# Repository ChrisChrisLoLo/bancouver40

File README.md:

# Zine Machine

> **🚧 Work in progress — not ready for fab yet.**
> Nothing here has been built or tested on real hardware. The v3 main board is routed and passes DRC, but its fab
> outputs and the "verify before ordering" checks are still open. Don't order boards from these files yet.

A pocket Linux computer built around a 40% keyboard: the [bancouver40](https://github.com/ChrisChrisLoLo/bancouver40)
4×10 Choc keyboard, a [PocketBeagle 2 Industrial](https://www.beagleboard.org/boards/pocketbeagle-2-industrial)
and a 4.58″ 320×960 bar display, battery powered, in an open 3D-printed tray.

*Blender renders of the v3 design: the routed main board from KiCad, the printed tray and display chassis, and
keycaps carrying the stock bancouver40 layers. The interactive page (<https://elevenarms.github.io/zinemachine0/>)
still shows the earlier v2 layout.*

## What it is (v3)

| | |
|---|---|
| Computer | PocketBeagle 2 Industrial (TI AM6254, 1 GB DDR4, 64 GB eMMC, −40…85 °C), face-down on its low-profile 3.55 mm sockets, USB-C out through the rear wall |
| Keyboard | 40 Kailh Choc v1 keys (4×10 ortholinear, CFX caps) plus three red/yellow/blue **mode keys**; switches soldered, no hot-swap |
| Key scanning | the PocketBeagle's own Cortex-M4F reads every key directly through six chained 74HC165s on its MCU-domain pins: no matrix, no diodes, full rollover |
| Display | 4.58″ 320×960 IPS bar panel (ST7701S), RGB565 over the AM62's VOUT0 + 3-wire SPI init, TPS61165 backlight boost |
| USB | FE1.1s hub on the PocketBeagle's USB1, two rear USB-A ports (500 mA each, TPS2051B) |
| Power | 1S LiPo (about 9 × 40 × 70 mm, ~2.5–3 Ah) under the display; IP5306 charger/5 V boost with its own rear charging USB-C; chunky slide switch; charge, power and boot LEDs |
| Audio | ES8388 codec over I2S: headset jack (headphones + mic, TRRS) and a line-out jack |
| Main board | 170 × 126 mm, 4 layers, all assembled parts on the top side; routed, DRC clean |
| Enclosure | open printed tray (175.2 × 131.2 × 12.5 mm) the whole assembly sits in; a printed display chassis holds the panel and boxes and clamps the battery; about 21 mm tall overall |

Keycap legends: base layer in the centre, Layer 1 (hold **L1**: numbers, brackets, arrows) top right in blue,
Layer 2 (hold **Space**: shifted symbols) top left in green, Layer 3 (both: F-keys, volume, Del, Boot) bottom right
in orange, hold functions bottom left.

## Repository layout

| Path | Contents |
|---|---|
| `pcb/bancouver40_pb2/` | the main board, KiCad 10 project: [v3 spec](pcb/bancouver40_pb2/DESIGN_v3.md) (positions, pin map, blocks), schematic sheets, PCB, own footprints/symbols (`zm_v3.*`), fab file |
| `tools/zm_v3/` | scripts that generate the v3 schematic and board from `design.py` and reproduce the routing (`krt_route.sh`, `finish.sh`) |
| `mech/` | FreeCAD scripts and parts: `tray`, `display_chassis` (both with fab files), `pb2_envelope` (light PocketBeagle model), `zine_concept` (whole-device layout with legends and exploded view), `fitcheck_board` (board STEP vs. mechanics) |
| `mech/render/` | Blender render script and output (`blender -b -P mech/render/zine_render.py -- 128 hero exploded`) |
| `case/pocketbeagle2/models/industrial/` | PocketBeagle 2 Industrial references: Rev A schematic, dimension drawing, [header pinout CSV](case/pocketbeagle2/models/industrial/pb2_header_pinout.csv), SysConfig |
| `case/pocketbeagle2/` | the earlier v2 case (SolidCraft), kept for reference |
| `bom/`, `site/`, `tools/pocketbeagle2/` | v2 BOM, the interactive page, and the v2 generator scripts |
| everything else | the upstream bancouver40 repository, unchanged ([original README](README-bancouver40.md)) |

Large files that are rebuilt by scripts or downloaded (the 110 MB PocketBeagle STEP conversion, assembly STEP/GLB
outputs) are git-ignored; see `.gitignore`.

## Status / open items

- Main board: silkscreen cleanup, fab outputs and README (stage 4).
- Charger choice: plain IP5306 (charge LEDs work with the device off; used now) or IP5306-I2C (Linux reads charge state).
- Check the PJ-327A headset jack's pin assignment with a plug and a meter.
- The fab stocks only 75 of the GCT USB1046 USB-A ports.
- Power budget is tight: ~2.3 A worst case against the IP5306's 2.1–2.4 A.
- Choose the battery cell and the slide switch, and decide what the three mode keys do.
- Software: M4F key-scan firmware + RPMsg-to-uinput service, device-tree overlay for the panel, codec and hub.
- From v2, still open: the display FPC pinout/contact side and fold length against a real panel.

## Credits

- **bancouver40** — keyboard design, PCB, case and firmware by **ChrisChrisLoLo (sporewoh)**:
  <https://github.com/ChrisChrisLoLo/bancouver40>, GPL-3.0. This project is a fork of it and everything in
  `pcb/bancouver40_pb2` starts from that board. The original README is kept as [README-bancouver40.md](README-bancouver40.md).
- **PocketBeagle 2 / PocketBeagle 2 Industrial** — hardware, schematic, drawings and 3D model by **BeagleBoard.org**. The STEP model
  (`case/pocketbeagle2/models/pocketbeagle2_v03_21_EVT.stp`, from <https://openbeagle.org/pocketbeagle/pocketbeagle-2>)
  is © BeagleBoard.org Foundation, [CC BY-SA 4.0](https://creativecommons.org/licenses/by-sa/4.0/); its web conversion is shared under the same licence.
  Pin functions come from the [PocketBeagle 2 documentation](https://docs.beagleboard.org/boards/pocketbeagle-2/).
- **KiCad** and the **KiCad libraries** — footprints and 3D component models (CC BY-SA 4.0 with the KiCad library exception), <https://www.kicad.org/>.
- **SolidCraft** (tangency-labs) — the case was modelled through SolidCraft's MCP server, <https://solidcraft.io/>.
- **Freerouting** — autorouting of the v2 display bus, <https://github.com/freerouting/freerouting> (not bundled).
- **KiCadRoutingTools** — routing of the v3 main board (built from source, not bundled).
- **FreeCAD** — the v3 tray, display chassis and fit checks; **Blender** — the renders.
- **three.js** (MIT) for the 3D page; **JetBrains Mono** and **Space Grotesk** (SIL OFL) via Google Fonts.
- **QMK** / **Vial** — keyboard firmware (GPL), as shipped by the upstream repo.
- Reference documents (linked, not redistributed): Maxen MX-046HS40FS-N01 / BuyDisplay ER-TFT4.58-1 panel drawing,
  Sitronix ST7701S and TI TPS61165 datasheets, Amphenol F32Q/F32R drawings.
- Design work assisted by Claude Code (Anthropic).

## License

GPL-3.0, inherited from bancouver40 (see [LICENSE](LICENSE)). The PocketBeagle 2 model and its derivatives are
CC BY-SA 4.0 (see [case/pocketbeagle2/models/README.md](case/pocketbeagle2/models/README.md)).

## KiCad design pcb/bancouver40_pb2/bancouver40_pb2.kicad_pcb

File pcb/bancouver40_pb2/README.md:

# Zine Machine v0 — PCB notes

> **Work in progress — not ready for fab.**

bancouver40 + PocketBeagle 2 + 4.58" 320x960 bar display

A variant of the bancouver40 with the board and case extended 48 mm north to carry a
[PocketBeagle 2](https://docs.beagleboard.org/boards/pocketbeagle-2/) and a 4.58" 320x960 IPS bar TFT
(ST7701S; e.g. [Maxen MX-046HS40FS-N01](https://maxen-lcddisplay.com/product/4-6-inch-bar-type-tft-display/),
BuyDisplay ER-TFT4.58-1 / Tailor Pixels TTG046XVS-01 — same 118.8 x 41.57 x 2.5 mm outline).
The keyboard matrix and ATmega32U4 are unchanged; the 32U4 is a USB keyboard wired into the
PocketBeagle's second USB port, so the stock QMK/Vial firmware works as-is.

The first version (2" Waveshare SPI LCD) is kept in `v1_2in_lcd/` and `case/pocketbeagle2/v1_2in_lcd/`.

## What changed on the PCB

| | |
|---|---|
| Outline | 170 x 116 mm (was 170 x 68), USB tab removed |
| Removed | J1 USB-C receptacle, R2/R3 (CC 5k1) |
| U2 | PocketBeagle 2 on the PocketBeagle header grid (`Module:BeagleBoard_PocketBeagle`), USB-C toward the left edge |
| J3 | 40-pin 0.5 mm FPC connector, Amphenol F32Q-1A7H1-11040 (top contact); F32R (bottom contact) has the identical land pattern |
| U3 + L1, D41, C8-C10, R7, R8 | TPS61165 white-LED boost for the backlight (2 x 4 LEDs, 11.2-13.2 V), 0.2 V / 5.1 Ω ≈ 39 mA, PWM dimming |
| H11-H13 | M2x15 standoffs that clamp the PCB to the case and hold the bezel |

Routing: the USB/VBUS links and the J1-removal repairs are hand-placed (`pcb_route.py`); the panel
bus and backlight are autorouted with Freerouting 2.5 restricted to the new nets (the keyboard's
copper is exported as fixed and never re-imported), then both layers are poured with GND and stitched.

### Display interface

The AM6254's DSS drives the panel as parallel RGB565 (DPI) on VOUT0; the ST7701S is initialised over
3-wire SPI. With the panel in 18-bit mode (MDT=1) DB17..12 = R5..R0, DB11..6 = G5..G0, DB5..0 = B5..B0:

| Panel (J3 pin) | PocketBeagle 2 | | Panel (J3 pin) | PocketBeagle 2 |
|---|---|---|---|---|
| DB17-DB13 (33-29) | VOUT0_D15..D11 = P2.34, P1.31, P2.30, P2.32, P1.33 | | PCLK (12) | P2.17 |
| DB12, DB0 (28, 16) | GND (R/B LSBs) | | DE (13) | P1.29 |
| DB11-DB6 (27-22) | VOUT0_D10..D5 = P1.36, P2.35, P2.18, P2.33, P2.24, P1.20 | | VSYNC / HSYNC (14 / 15) | P2.22 / P2.28 |
| DB5-DB1 (21-17) | VOUT0_D4..D0 = P2.20, P2.08, P2.06, P2.04, P2.02 | | SDA / SCK / CS (9 / 10 / 11) | P2.25 / P2.29 / P2.31 (SPI0) |
| VCI (5) | +3V3 (P2.23) | | RESET (6) | P2.10 (GPIO0_91) |
| LEDA / LEDK (1 / 2-3) | boost output / current sense | | Backlight PWM | P2.01 (ECAP2 APWM, mode 2) |

Pin functions verified against the PocketBeagle 2 pinmux tables
(docs.beagleboard.org/boards/pocketbeagle-2/04-expansion.html). **VOUT0_D10 and D11 share their header
pins with I2C1 (P1.36/P1.33 have a second ball each): leave the I2C1 balls unmuxed.** The panel's touch
pins (35-39) are left unconnected.

USB and power are as before: D-/D+ to P1.09/P1.11 (USB1 host), P1.24 VOUT -> F1 -> the keyboard's +5V
(also feeds the backlight boost), P1.05 USB1_VBUS left open.

Checks (KiCad 10.0.7 `kicad-cli`): 0 unconnected items; ERC and schematic parity show only what the
original project already has (KiCad 6 -> 10 auto-net naming, R4/R5 value fields, C3 thermal, U1 PC6).
Minimum track width is 0.12 mm (Freerouting necks to 0.187 mm, once 0.125 mm, at the 0.5 mm-pitch pads).

## Stack-up (case coordinates, z from the case bottom)

| z (mm) | |
|---|---|
| 0-1 | case floor |
| 4.5-6.1 | keyboard PCB on the original bosses + 3 through-bosses |
| 6.1-~8 | J3 connector; the panel FPC returns under the panel at ~7.4 |
| 6.1-12 | Choc v1 switches; CFX keycaps 12-15.6 |
| 6.1-14.6 | PocketBeagle 2's own 2x18 female sockets (8.5 mm) on a 2x18 male header inserted from under the PCB |
| 14.6-16.1 | PocketBeagle 2 board; tallest part under the panel 17.2, USB-C 15.1-19.3 (official BeagleBoard STEP) |
| 18.6-21.1 | bar panel, glued to the bezel's underside inside a locating frame |
| 21.1-22.6 | bezel, sitting on 3 x M2x15 standoffs (keyboard walls stay at 12.5) |

## Before ordering — verify these

1. **FPC contact side.** The panel drawing shows the stiffener on the front of the unfolded tail, so after
   the 180° fold under the panel the contacts face up -> top-contact F32Q. If your panel's contacts are on
   the other side, fit the F32R (same footprint).
2. **FPC fold length.** The 30 mm tail is budgeted as 1 mm straight + ~19 mm fold (r ≈ 6.1) + ~10 mm
   return into J3 (cable end at x ≈ 209.8 KiCad). Lay a real panel on a printout before committing.
3. **PocketBeagle mounting.** It plugs in on its factory sockets: fit a 2x18 male header from *under* the
   keyboard PCB (plastic below, pins up), trimmed to < 3 mm below the PCB (floor clearance). The design
   was checked against BeagleBoard's `pocketbeagle2_v03_21_EVT.stp` (an EVT revision).
4. **P1.24 VOUT is 5 V on PocketBeagle 2** (classic: `VOUT-5V`; PB2 docs just say `VOUT`). Measure it.
5. **PocketBeagle 2 USB-C position** (case opening 14 mm wide, centred on the short edge) and the
   microSD — it is under the panel now, so flash the card before assembly.
6. **Software:** a device-tree overlay for the DSS (RGB565, PCLK on P2.17, panel timings) plus the
   ST7701S init sequence (the vendor sends one; Linux has `panel-sitronix-st7701`).

## Regenerate

```sh
tools/pocketbeagle2/build_pcb.sh pcb/bancouver40_cfx/bancouver40_cfx.kicad_pcb pcb/bancouver40_pb2/bancouver40_pb2.kicad_pcb
python3 tools/pocketbeagle2/sch_update.py pcb/bancouver40_cfx/bancouver40_cfx.kicad_sch pcb/bancouver40_pb2/bancouver40_pb2.kicad_sch
python3 tools/pocketbeagle2/case_v2.py case/pocketbeagle2      # SolidCraft command scripts
```

Needs KiCad 10 (`~/Applications/KiCad`), Java >= 25 (`brew install openjdk`) and
`~/.local/share/freerouting/freerouting-2.5.0.jar`. Freerouting is not deterministic: the script retries
until a run finishes fully routed, so each rebuild gives slightly different (equally valid) copper.

The interactive site is `site/` (serve the repo root, open `/site/`). The case is `case/pocketbeagle2/bancouver40_pb2.solidcraft`; `stage1..5*.json` built it through the
SolidCraft MCP server (`tools/pocketbeagle2/sc.py`). `REF_*` bodies (PCB, PocketBeagle, panel, FPC,
connector, standoffs, 40 Choc switches and CFX keycaps) are fit-check placeholders, left out of the
STL/STEP print files.

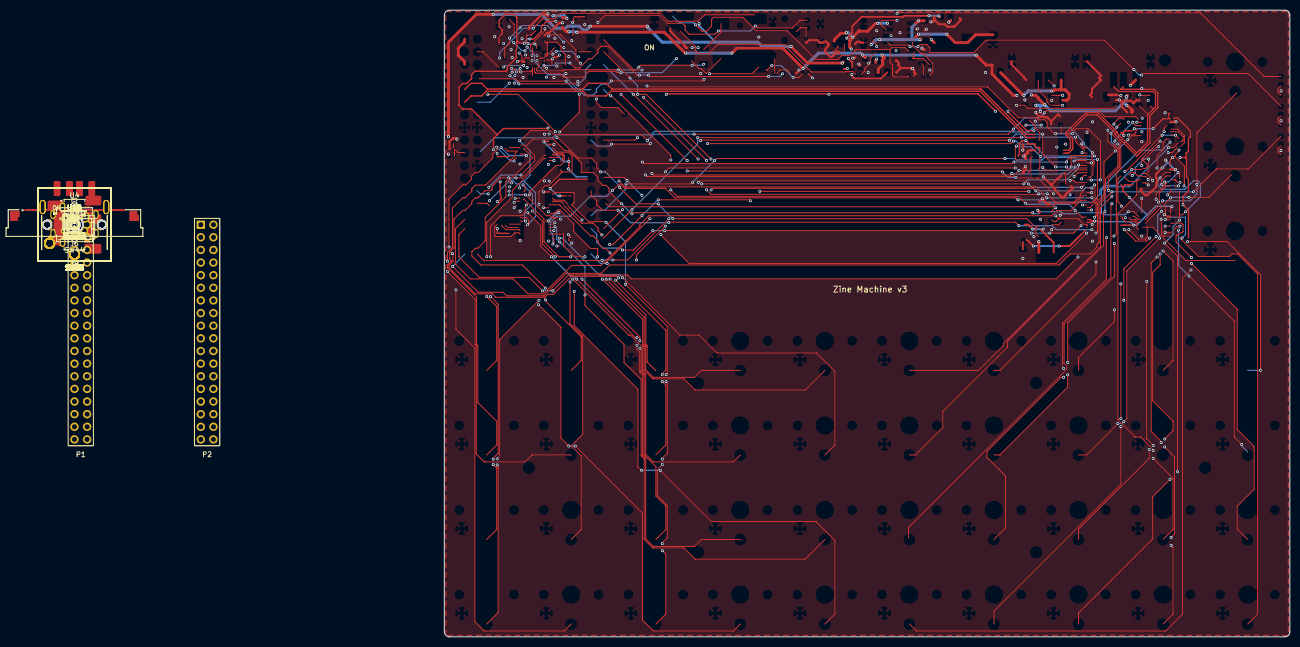
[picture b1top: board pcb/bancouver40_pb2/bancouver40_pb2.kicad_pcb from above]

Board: 4 copper layers, 170.0 x 126.0 mm, 188 parts (0 on the bottom side), 156 nets.

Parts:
C1: 4.7uF 25V; C_0805_2012Metric
C2: 1uF 50V; C_0805_2012Metric
C3: 220nF; C_0603_1608Metric
C10, C12, C14, C16, C18, C27, C31, C40, C41, C42, C44, C46, C49, C52, C60, C61, C62, C63, C64, C65: 100nF; C_0402_1005Metric
C11, C13, C20, C21, C43, C45, C47, C48, C50, C51, C55, C58, C59, C66: 10uF; C_0603_1608Metric
C15, C17, C56, C57: 100uF; C_1206_3216Metric
C22, C23, C24, C25, C26, C28, C29: 22uF; C_0805_2012Metric
C30, C53, C67: 1uF; C_0402_1005Metric
C54: 10nF; C_0402_1005Metric
D1: B5819W; D_SOD-123
D2: red CHG; LED_0603_1608Metric
D3: green PWR; LED_0603_1608Metric
D4: yellow BOOT; LED_0603_1608Metric
H1, H2, H3, H4, H5, H6: M2; MountingHole_2.2mm_M2_ISO7380
H7, H8, H9, H10: M2; MountingHole_2.2mm_M2
J3: F32Q-1A7H1-11040; Amphenol_F32Q-1A7x1-11040_1x40-1MP_P0.5mm_Horizontal
J5: LiPo 1S; JST_PH_B2B-PH-K_1x02_P2.00mm_Vertical
J6: USB-C 6P; USB_C_Receptacle_6P_ShouHan
J7, J8: USB-A; USB_A_GCT_USB1046
J9: Headset (CTIA); Jack_3.5mm_PJ-327A_5JJ
J10: Line out; Jack_3.5mm_PJ-320A-3P_DIP
L1: 22uH; L_Changjiang_FNR4030S
L2: 1uH; L_Sunlord_MWSA0603S
Q1: AO3401A; SOT-23
Q2: AO3400A; SOT-23
R1: 5.1R 1%; R_0603_1608Metric
R2, R26, R53: 100k; R_0402_1005Metric
R10: 2.7k 1%; R_0603_1608Metric
R11, R12, R13, R27, R47, R48: 10k; R_0402_1005Metric
R20, R21: 5.1k; R_0402_1005Metric
R22: 2R; R_0603_1608Metric
R23: 0.5R; R_0603_1608Metric
R24, R25, R30, R33, R51: 1k; R_0402_1005Metric
R28, R31, R32: 1M; R_0402_1005Metric
R29: 470k; R_0402_1005Metric
R40, R41, R42, R43, R44, R60, R61: 33R; R_0402_1005Metric
R45, R46, R52: 2.2k; R_0402_1005Metric
R49, R50: 47k; R_0402_1005Metric
RN1, RN2, RN3, RN4, RN5, RN6, RN7, RN8, RN9, RN10, RN11, RN12: 4x10k; R_Array_Convex_4x0603
SW1, SW2, SW3, SW4, SW5, SW6, SW7, SW8, SW9, SW10, SW11, SW12, SW13, SW14, SW15, SW16, SW17, SW18, SW19, SW20, SW21, SW22, SW23, SW24, SW25, SW26, SW27, SW28, SW29, SW30, SW31, SW32, SW33, SW34, SW35, SW36, SW37, SW38, SW39, SW40, SW41, SW42, SW43: Choc_v1; SW_Kailh_Choc_V1_Plain
SW44: SK22D02G4; SW_Slide_DPDT_SK22D02G4_Angled
TP1: M4F_SPARE; TestPoint_Pad_D1.0mm
U2: PocketBeagle 2 Industrial; PocketBeagle2_FaceDown
U3: TPS61165DBVR; SOT-23-6
U4: FE1.1s; SSOP-28_3.9x9.9mm_P0.635mm
U5, U6: TPS2051BDBVR; SOT-23-5
U7, U8: USBLC6-2SC6; SOT-23-6
U9: IP5306; SOIC-8-1EP_3.9x4.9mm_P1.27mm_EP2.29x3mm
U10, U11, U12, U13, U14, U15: 74HC165; TSSOP-16_4.4x5mm_P0.65mm
U16: TPS73633DBVR; SOT-23-5
U17: ES8388; QFN-28-1EP_4x4mm_P0.4mm_EP2.4x2.4mm
X1: 12.288MHz; Oscillator_SMD_Abracon_ASE-4Pin_3.2x2.5mm
Y1: 12MHz; Crystal_SMD_3225-4Pin_3.2x2.5mm

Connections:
+3V3: C40.1, C41.1, C42.1, C43.1, C60.1, C61.1, C62.1, C63.1, C64.1, C65.1, J3.5, R45.1, R46.1, R53.1, RN1.5, RN1.6, RN1.7, RN1.8, RN2.5, RN2.6, RN2.7, RN2.8, RN3.5, RN3.6, RN3.7, RN3.8, RN4.5, RN4.6, RN4.7, RN4.8, RN5.5, RN5.6, RN5.7, RN5.8, RN6.5, RN6.6, RN6.7, RN6.8, RN7.5, RN7.6, RN7.7, RN7.8, RN8.5, RN8.6, RN8.7, RN8.8, RN9.5, RN9.6, RN9.7, RN9.8, RN10.5, RN10.6, RN10.7, RN10.8, RN11.5, RN11.6, RN11.7, RN11.8, RN12.5, RN12.6, RN12.7, RN12.8, U2.14, U2.59, U10.16, U11.16, U12.16, U13.16, U14.16, U15.16, U17.2, U17.3, X1.1, X1.4
+5V_BOOST: C24.1, C25.1, C26.1, C27.2, Q1.2, R26.2, U9.8
+5V_SYS: C1.1, C11.1, C12.1, C16.1, C18.1, C28.1, C29.1, C53.1, L1.1, Q1.3, U2.1, U2.5, U3.1, U4.20, U5.4, U5.5, U6.4, U6.5, U16.1, U16.3
/Audio/CODEC_ADCVREF: C50.1, U17.19
/Audio/CODEC_VMID: C51.1, C52.1, U17.20
/Audio/CODEC_VREF: C48.1, C49.1, U17.10
/Audio/HP_L: C56.2, J9.2, R47.1
/Audio/HP_L_C: C56.1, U17.12
/Audio/HP_R: C57.2, J9.4, R48.1
/Audio/HP_R_C: C57.1, U17.11
/Audio/I2S_ADC_C: R43.1, U17.8
/Audio/I2S_BCLK_C: R41.1, U17.5
/Audio/I2S_DAC_C: R44.2, U17.6
/Audio/I2S_LRCK_C: R42.1, U17.7
/Audio/LDO_NR: C54.1, U16.4
/Audio/LO_L: C58.2, J10.4, R49.1
/Audio/LO_L_C: C58.1, U17.15
/Audio/LO_R: C59.2, J10.2, R50.1
/Audio/LO_R_C: C59.1, U17.14
/Audio/MCLK: R40.2, U17.1
/Audio/MCLK_OSC: R40.1, X1.3
/Audio/MIC: C67.1, J9.1, R52.2
/Audio/MIC_BIAS_F: C66.1, R51.2, R52.1
/Audio/MIC_IN: C67.2, U17.24
/Keys and scan chain/K00: RN1.1, SW1.1, U10.11
/Keys and scan chain/K01: RN2.1, SW2.1, U10.3
/Keys and scan chain/K02: RN3.1, SW3.1, U11.11
/Keys and scan chain/K03: RN4.1, SW4.1, U11.3
/Keys and scan chain/K04: RN5.1, SW5.1, U12.11
/Keys and scan chain/K05: RN7.1, SW6.1, U13.11
/Keys and scan chain/K06: RN8.1, SW7.1, U13.3
/Keys and scan chain/K07: RN9.1, SW8.1, U14.11
/Keys and scan chain/K08: RN10.1, SW9.1, U14.3
/Keys and scan chain/K09: RN11.1, SW10.1, U15.11
/Keys and scan chain/K10: RN1.2, SW11.1, U10.12
/Keys and scan chain/K11: RN2.2, SW12.1, U10.4
/Keys and scan chain/K12: RN3.2, SW13.1, U11.12
/Keys and scan chain/K13: RN4.2, SW14.1, U11.4
/Keys and scan chain/K14: RN5.2, SW15.1, U12.12
/Keys and scan chain/K15: RN7.2, SW16.1, U13.12
/Keys and scan chain/K16: RN8.2, SW17.1, U13.4
/Keys and scan chain/K17: RN9.2, SW18.1, U14.12
/Keys and scan chain/K18: RN10.2, SW19.1, U14.4
/Keys and scan chain/K19: RN11.2, SW20.1, U15.12
/Keys and scan chain/K20: RN1.3, SW21.1, U10.13
/Keys and scan chain/K21: RN2.3, SW22.1, U10.5
/Keys and scan chain/K22: RN3.3, SW23.1, U11.13
/Keys and scan chain/K23: RN4.3, SW24.1, U11.5
/Keys and scan chain/K24: RN5.3, SW25.1, U12.13
/Keys and scan chain/K25: RN7.3, SW26.1, U13.13
/Keys and scan chain/K26: RN8.3, SW27.1, U13.5
/Keys and scan chain/K27: RN9.3, SW28.1, U14.13
/Keys and scan chain/K28: RN10.3, SW29.1, U14.5
/Keys and scan chain/K29: RN11.3, SW30.1, U15.13
/Keys and scan chain/K30: RN1.4, SW31.1, U10.14
/Keys and scan chain/K31: RN2.4, SW32.1, U10.6
/Keys and scan chain/K32: RN3.4, SW33.1, U11.14
/Keys and scan chain/K33: RN4.4, SW34.1, U11.6
/Keys and scan chain/K34: RN5.4, SW35.1, U12.14
/Keys and scan chain/K35: RN7.4, SW36.1, U13.14
/Keys and scan chain/K36: RN8.4, SW37.1, U13.6
/Keys and scan chain/K37: RN9.4, SW38.1, U14.14
/Keys and scan chain/K38: RN10.4, SW39.1, U14.6
/Keys and scan chain/K39: RN11.4, SW40.1, U15.14
/Keys and scan chain/KEY_CLK: R60.2, U10.2, U11.2, U12.2, U13.2, U14.2, U15.2
/Keys and scan chain/KEY_S1: U10.10, U11.9
/Keys and scan chain/KEY_S2: U11.10, U12.9
/Keys and scan chain/KEY_S3: U12.10, U13.9
/Keys and scan chain/KEY_S4: U13.10, U14.9
/Keys and scan chain/KEY_S5: U14.10, U15.9
/Keys and scan chain/KEY_SHLD: R61.2, U10.1, U11.1, U12.1, U13.1, U14.1, U15.1
/Keys and scan chain/K_BLU: RN12.3, SW43.1, U15.5
/Keys and scan chain/K_RED: RN12.1, SW41.1, U15.3
/Keys and scan chain/K_YEL: RN12.2, SW42.1, U15.4
/Keys and scan chain/U12_SPE: RN6.1, U12.3
/Keys and scan chain/U12_SPF: RN6.2, U12.4
/Keys and scan chain/U12_SPG: RN6.3, U12.5
/Keys and scan chain/U12_SPH: RN6.4, U12.6
/Keys and scan chain/U15_SPH: RN12.4, U15.6
/PocketBeagle 2 + display/BL_COMP: C3.1, U3.5
/PocketBeagle 2 + display/BL_LEDA: C2.1, D1.1, J3.1
/PocketBeagle 2 + display/BL_LEDK: J3.2, J3.3, R1.1, U3.6
/PocketBeagle 2 + display/BL_PWM: R2.1, U2.6, U3.2
/PocketBeagle 2 + display/BL_SW: D1.2, L1.2, U3.3
/PocketBeagle 2 + display/BOOT_LED_K: D4.1, R33.1
/PocketBeagle 2 + display/LCD_CS: J3.11, U2.67
/PocketBeagle 2 + display/LCD_DE: J3.13, U2.29
/PocketBeagle 2 + display/LCD_HSYNC: J3.15, U2.64
/PocketBeagle 2 + display/LCD_PCLK: J3.12, U2.53
/PocketBeagle 2 + display/LCD_RESET: J3.6, U2.46
/PocketBeagle 2 + display/LCD_SCK: J3.10, U2.65
/PocketBeagle 2 + display/LCD_SDA: J3.9, U2.61
/PocketBeagle 2 + display/LCD_VSYNC: J3.14, U2.58
/PocketBeagle 2 + display/LED_BOOT: D4.2, U2.35
/PocketBeagle 2 + display/M4F_SPARE: TP1.1, U2.43
/PocketBeagle 2 + display/VOUT_D0: J3.17, U2.38
/PocketBeagle 2 + display/VOUT_D1: J3.18, U2.40
/PocketBeagle 2 + display/VOUT_D2: J3.19, U2.42
/PocketBeagle 2 + display/VOUT_D3: J3.20, U2.44
/PocketBeagle 2 + display/VOUT_D4: J3.21, U2.56
/PocketBeagle 2 + display/VOUT_D5: J3.22, U2.20
/PocketBeagle 2 + display/VOUT_D6: J3.23, U2.60
/PocketBeagle 2 + display/VOUT_D7: J3.24, U2.69
/PocketBeagle 2 + display/VOUT_D8: J3.25, U2.54
/PocketBeagle 2 + display/VOUT_D9: J3.26, U2.71
/PocketBeagle 2 + display/VOUT_D10: J3.27, U2.36
/PocketBeagle 2 + display/VOUT_D11: J3.29, U2.33
/PocketBeagle 2 + display/VOUT_D12: J3.30, U2.68
/PocketBeagle 2 + display/VOUT_D13: J3.31, U2.66
/PocketBeagle 2 + display/VOUT_D14: J3.32, U2.31
/PocketBeagle 2 + display/VOUT_D15: J3.33, U2.70
/USB hub and power/BAT_SNUB: C23.1, R23.2
/USB hub and power/CHG_CC1: J6.A5, R20.1
/USB hub and power/CHG_CC2: J6.B5, R21.1
/USB hub and power/CHG_LED_K: D2.1, R24.1
/USB hub and power/CHG_SNUB: C21.1, R22.2
/USB hub and power/CHG_SW: L2.1, U9.7
/USB hub and power/HUB_DRV: R13.1, U4.22
/USB hub and power/HUB_REXT: R10.1, U4.14
/USB hub and power/HUB_RST: C10.1, R11.2, U4.17
/USB hub and power/HUB_XI: U4.3, Y1.1
/USB hub and power/HUB_XO: U4.2, Y1.3
/USB hub and power/LED_CHG: D2.2, U9.2
/USB hub and power/LED_PWR: D3.2, U9.4
/USB hub and power/PWR_GATE: C27.1, Q1.1, R26.1, R27.2
/USB hub and power/PWR_KEY: R30.2, U9.5
/USB hub and power/PWR_KEY_C: C30.1, R28.1, SW44.6
/USB hub and power/PWR_KEY_D: Q2.3, R30.1
/USB hub and power/PWR_KEY_G: C30.2, Q2.1, R29.1
/USB hub and power/PWR_LED_K: D3.1, R25.1
/USB hub and power/PWR_SW: R27.1, SW44.2
/USB hub and power/USB1_N: J7.2, U4.10, U7.1, U7.6
/USB hub and power/USB1_P: J7.3, U4.11, U7.3, U7.4
/USB hub and power/USB1_VBUS: C15.1, J7.1, U5.1, U7.5
/USB hub and power/USB2_N: J8.2, U4.8, U8.1, U8.6
/USB hub and power/USB2_P: J8.3, U4.9, U8.3, U8.4
/USB hub and power/USB2_VBUS: C17.1, J8.1, U6.1, U8.5
/USB hub and power/USB_OC_N: R12.2, U4.26, U5.3, U6.3
AVDD_3V3: C44.1, C45.1, C46.1, C47.1, C55.1, R51.1, U16.5, U17.16, U17.17
GND: C1.2, C2.2, C3.2, C10.2, C11.2, C12.2, C13.2, C14.2, C15.2, C16.2, C17.2, C18.2, C20.2, C21.2, C22.2, C23.2, C24.2, C25.2, C26.2, C28.2, C29.2, C31.2, C40.2, C41.2, C42.2, C43.2, C44.2, C45.2, C46.2, C47.2, C48.2, C49.2, C50.2, C51.2, C52.2, C53.2, C54.2, C55.2, C60.2, C61.2, C62.2, C63.2, C64.2, C65.2, C66.2, J3.4, J3.16, J3.28, J3.34, J3.40, J3.MP, J5.2, J6.7, J6.A12, J6.B12, J7.4, J7.SH, J8.4, J8.SH, J9.3, J10.3, Q2.2, R1.2, R2.2, R10.2, R13.2, R20.2, R21.2, R24.2, R25.2, R28.2, R29.2, R32.2, R33.2, R47.2, R48.2, R49.2, R50.2, SW1.2, SW2.2, SW3.2, SW4.2, SW5.2, SW6.2, SW7.2, SW8.2, SW9.2, SW10.2, SW11.2, SW12.2, SW13.2, SW14.2, SW15.2, SW16.2, SW17.2, SW18.2, SW19.2, SW20.2, SW21.2, SW22.2, SW23.2, SW24.2, SW25.2, SW26.2, SW27.2, SW28.2, SW29.2, SW30.2, SW31.2, SW32.2, SW33.2, SW34.2, SW35.2, SW36.2, SW37.2, SW38.2, SW39.2, SW40.2, SW41.2, SW42.2, SW43.2, SW44.1, SW44.7, SW44.8, U2.15, U2.16, U2.22, U2.51, U2.57, U3.4, U4.1, U5.2, U6.2, U7.2, U8.2, U9.9, U10.8, U10.15, U11.8, U11.15, U12.8, U12.15, U13.8, U13.15, U14.8, U14.15, U15.8, U15.10, U15.15, U16.2, U17.4, U17.13, U17.18, U17.26, U17.29, X1.2, Y1.2, Y1.4
HP_DET: J9.5, R53.2, U2.8
HUB_3V3: C13.1, C14.1, R11.1, R12.1, U4.18, U4.19, U4.21
I2C_SCL: R45.2, U2.45, U17.28
I2C_SDA: R46.2, U2.47, U17.27
I2S_ADC: R43.2, U2.12
I2S_BCLK: R41.2, U2.37
I2S_DAC: R44.1, U2.39
I2S_LRCK: R42.2, U2.4
KEY_CLK_PB: R60.1, U2.26
KEY_QH: U2.41, U10.9
KEY_SHLD_PB: R61.1, U2.28
USB_UP_N: U2.9, U4.15
USB_UP_P: U2.11, U4.16
VBAT: C22.1, J5.1, L2.2, R23.1, R31.1, SW44.5, U9.3, U9.6
VBAT_SENSE: C31.1, R31.2, R32.1, U2.19
VIN_CHG: C20.1, J6.A9, J6.B9, R22.1, U9.1

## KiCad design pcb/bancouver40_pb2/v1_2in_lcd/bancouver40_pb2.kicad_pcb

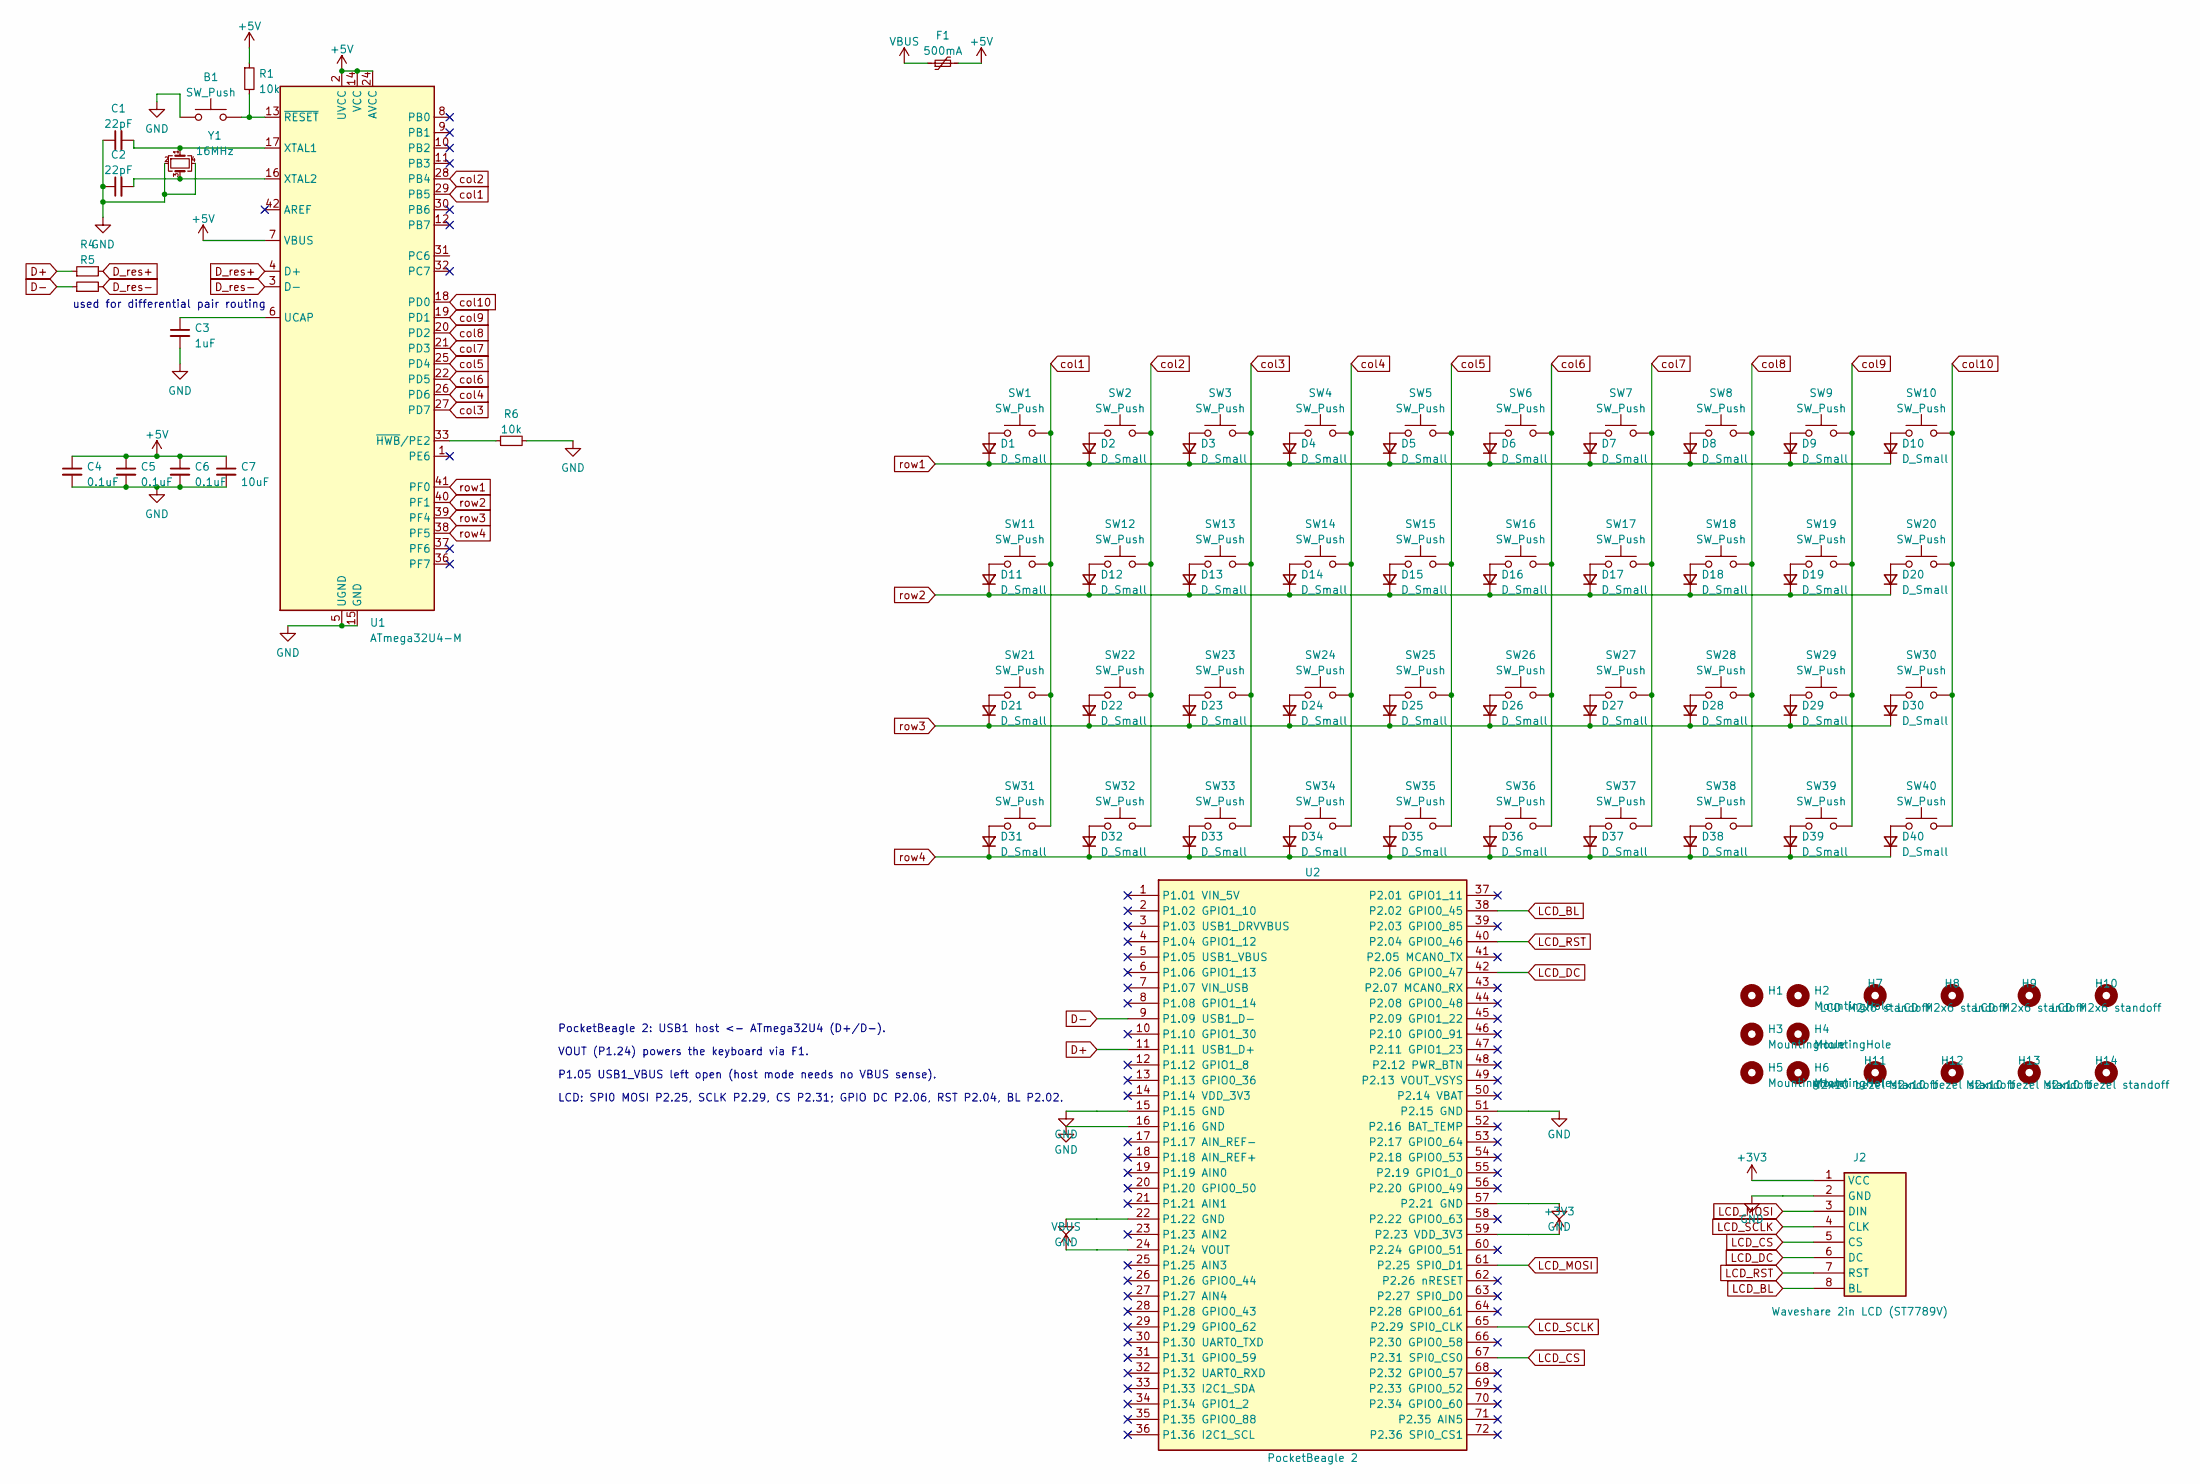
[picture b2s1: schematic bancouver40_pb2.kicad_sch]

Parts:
B1: SW_Push; SW_SPST_SKQG_WithoutStem
C1, C2: 22pF
C3: 1uF
C4, C5, C6: 0.1uF
C7: 10uF
D1, D2, D3, D4, D5, D6, D7, D8, D9, D10, D11, D12, D13, D14, D15, D16, D17, D18, D19, D20, D21, D22, D23, D24, D25, D26, D27, D28, D29, D30, D31, D32, D33, D34, D35, D36, D37, D38, D39, D40: D_Small
F1: 500mA
H1: (no value)
H2, H3, H4, H5, H6: MountingHole
H7, H8, H9, H10: LCD M2x6 standoff; MountingHole_2.2mm_M2
H11, H12, H13, H14: M2x10 bezel standoff; MountingHole_2.2mm_M2
J2: Waveshare 2in LCD (ST7789V); PinHeader_1x08_P2.54mm_Vertical
R1, R6: 10k
R4, R5: (no value)
SW1, SW2, SW3, SW4, SW5, SW6, SW7, SW8, SW9, SW10, SW11, SW12, SW13, SW14, SW15, SW16, SW17, SW18, SW19, SW20, SW21, SW22, SW23, SW24, SW25, SW26, SW27, SW28, SW29, SW30, SW31, SW32, SW33, SW34, SW35, SW36, SW37, SW38, SW39, SW40: SW_Push; Kailh_socket_PG1350
U1: ATmega32U4-M; QFN-44-1EP_7x7mm_P0.5mm_EP5.2x5.2mm
U2: PocketBeagle 2; BeagleBoard_PocketBeagle
Y1: 16MHz; Crystal_SMD_3225-4Pin_3.2x2.5mm

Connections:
+3V3: J2.1 (VCC), U2.59 (P2.23 VDD_3V3)
+5V: C4.1, C5.1, C6.1, C7.1, F1.2, R1.1, U1.2 (UVCC), U1.7 (VBUS), U1.14 (VCC), U1.24 (AVCC), U1.34 (VCC), U1.44 (AVCC)
D+: R4.1, U2.11 (P1.11 USB1_D+)
D-: R5.1, U2.9 (P1.09 USB1_D-)
D_res+: R4.2, U1.4 (D+)
D_res-: R5.2, U1.3 (D-)
GND: B1.1, C1.1, C2.1, C3.2, C4.2, C5.2, C6.2, C7.2, J2.2 (GND), R6.2, U1.5 (UGND), U1.15 (GND), U1.23 (GND), U1.35 (GND), U1.43 (GND), U1.45 (GND), U2.15 (P1.15 GND), U2.16 (P1.16 GND), U2.22 (P1.22 GND), U2.51 (P2.15 GND), U2.57 (P2.21 GND), Y1.2, Y1.4
LCD_BL: J2.8 (BL), U2.38 (P2.02 GPIO0_45)
LCD_CS: J2.5 (CS), U2.67 (P2.31 SPI0_CS0)
LCD_DC: J2.6 (DC), U2.42 (P2.06 GPIO0_47)
LCD_MOSI: J2.3 (DIN), U2.61 (P2.25 SPI0_D1)
LCD_RST: J2.7 (RST), U2.40 (P2.04 GPIO0_46)
LCD_SCLK: J2.4 (CLK), U2.65 (P2.29 SPI0_CLK)
unnamed: B1.2, R1.2, U1.13 (~RESET)
unnamed: C1.2, U1.17 (XTAL1), Y1.1
unnamed: C2.2, U1.16 (XTAL2), Y1.3
unnamed: C3.1, U1.6 (UCAP)
unnamed: D1.2 (A), SW1.1
unnamed: D2.2 (A), SW2.1
unnamed: D3.2 (A), SW3.1
unnamed: D4.2 (A), SW4.1
unnamed: D5.2 (A), SW5.1
unnamed: D6.2 (A), SW6.1
unnamed: D7.2 (A), SW7.1
unnamed: D8.2 (A), SW8.1
unnamed: D9.2 (A), SW9.1
unnamed: D10.2 (A), SW10.1
unnamed: D11.2 (A), SW11.1
unnamed: D12.2 (A), SW12.1
unnamed: D13.2 (A), SW13.1
unnamed: D14.2 (A), SW14.1
unnamed: D15.2 (A), SW15.1
unnamed: D16.2 (A), SW16.1
unnamed: D17.2 (A), SW17.1
unnamed: D18.2 (A), SW18.1
unnamed: D19.2 (A), SW19.1
unnamed: D20.2 (A), SW20.1
unnamed: D21.2 (A), SW21.1
unnamed: D22.2 (A), SW22.1
unnamed: D23.2 (A), SW23.1
unnamed: D24.2 (A), SW24.1
unnamed: D25.2 (A), SW25.1
unnamed: D26.2 (A), SW26.1
unnamed: D27.2 (A), SW27.1
unnamed: D28.2 (A), SW28.1
unnamed: D29.2 (A), SW29.1
unnamed: D30.2 (A), SW30.1
unnamed: D31.2 (A), SW31.1
unnamed: D32.2 (A), SW32.1
unnamed: D33.2 (A), SW33.1
unnamed: D34.2 (A), SW34.1
unnamed: D35.2 (A), SW35.1
unnamed: D36.2 (A), SW36.1
unnamed: D37.2 (A), SW37.1
unnamed: D38.2 (A), SW38.1
unnamed: D39.2 (A), SW39.1
unnamed: D40.2 (A), SW40.1
unnamed: R6.1, U1.33 (~HWB/PE2)
VBUS: F1.1, U2.24 (P1.24 VOUT)
col1: SW1.2, SW11.2, SW21.2, SW31.2, U1.29 (PB5)
col2: SW2.2, SW12.2, SW22.2, SW32.2, U1.28 (PB4)
col3: SW3.2, SW13.2, SW23.2, SW33.2, U1.27 (PD7)
col4: SW4.2, SW14.2, SW24.2, SW34.2, U1.26 (PD6)
col5: SW5.2, SW15.2, SW25.2, SW35.2, U1.25 (PD4)
col6: SW6.2, SW16.2, SW26.2, SW36.2, U1.22 (PD5)
col7: SW7.2, SW17.2, SW27.2, SW37.2, U1.21 (PD3)
col8: SW8.2, SW18.2, SW28.2, SW38.2, U1.20 (PD2)
col9: SW9.2, SW19.2, SW29.2, SW39.2, U1.19 (PD1)
col10: SW10.2, SW20.2, SW30.2, SW40.2, U1.18 (PD0)
row1: D1.1 (K), D2.1 (K), D3.1 (K), D4.1 (K), D5.1 (K), D6.1 (K), D7.1 (K), D8.1 (K), D9.1 (K), D10.1 (K), U1.41 (PF0)
row2: D11.1 (K), D12.1 (K), D13.1 (K), D14.1 (K), D15.1 (K), D16.1 (K), D17.1 (K), D18.1 (K), D19.1 (K), D20.1 (K), U1.40 (PF1)
row3: D21.1 (K), D22.1 (K), D23.1 (K), D24.1 (K), D25.1 (K), D26.1 (K), D27.1 (K), D28.1 (K), D29.1 (K), D30.1 (K), U1.39 (PF4)
row4: D31.1 (K), D32.1 (K), D33.1 (K), D34.1 (K), D35.1 (K), D36.1 (K), D37.1 (K), D38.1 (K), D39.1 (K), D40.1 (K), U1.38 (PF5)

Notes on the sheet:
used for differential pair routing
PocketBeagle 2: USB1 host <- ATmega32U4 (D+/D-).
VOUT (P1.24) powers the keyboard via F1.
P1.05 USB1_VBUS left open (host mode needs no VBUS sense).
LCD: SPI0 MOSI P2.25, SCLK P2.29, CS P2.31; GPIO DC P2.06, RST P2.04, BL P2.02.

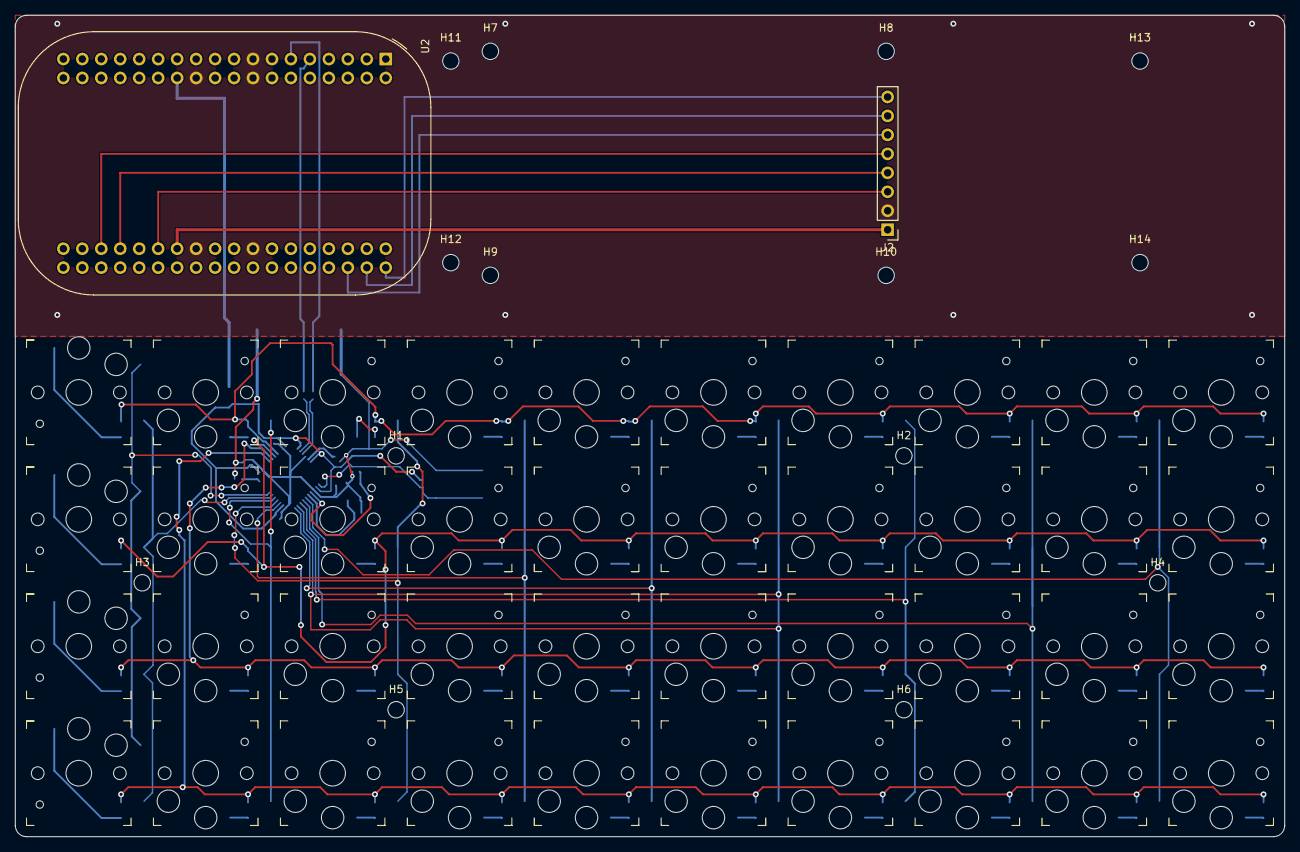
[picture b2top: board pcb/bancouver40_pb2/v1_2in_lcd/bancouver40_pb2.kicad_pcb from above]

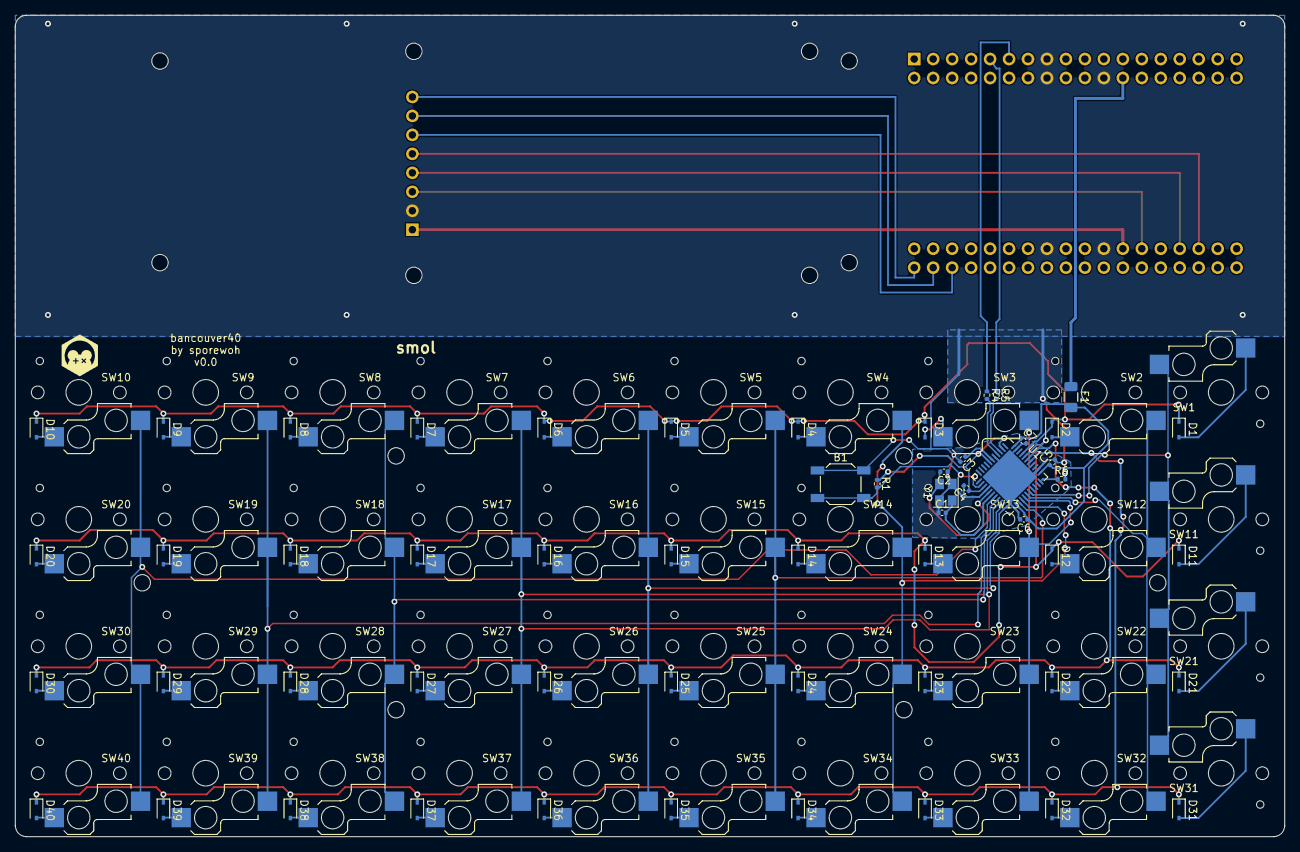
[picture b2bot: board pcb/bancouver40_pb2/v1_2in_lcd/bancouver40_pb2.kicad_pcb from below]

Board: 2 copper layers, 170.0 x 110.0 mm, 111 parts (55 on the bottom side), 73 nets.

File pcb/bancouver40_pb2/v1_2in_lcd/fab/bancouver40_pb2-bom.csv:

"Refs","Value","Footprint","Qty","DNP"
"B1","SW_Push","Button_Switch_SMD:SW_SPST_SKQG_WithoutStem","1",""
"C1","22pF","Capacitor_SMD:C_0402_1005Metric","1",""
"C2","22pF","Capacitor_SMD:C_0402_1005Metric","1",""
"C3","1uF","Capacitor_SMD:C_0402_1005Metric","1",""
"C4","0.1uF","Capacitor_SMD:C_0402_1005Metric","1",""
"C5","0.1uF","Capacitor_SMD:C_0402_1005Metric","1",""
"C6","0.1uF","Capacitor_SMD:C_0402_1005Metric","1",""
"C7","10uF","Capacitor_SMD:C_0402_1005Metric","1",""
"D1","D_Small","Diode_SMD:D_SOD-323","1",""
"D2","D_Small","Diode_SMD:D_SOD-323","1",""
"D3","D_Small","Diode_SMD:D_SOD-323","1",""
"D4","D_Small","Diode_SMD:D_SOD-323","1",""
"D5","D_Small","Diode_SMD:D_SOD-323","1",""
"D6","D_Small","Diode_SMD:D_SOD-323","1",""
"D7","D_Small","Diode_SMD:D_SOD-323","1",""
"D8","D_Small","Diode_SMD:D_SOD-323","1",""
"D9","D_Small","Diode_SMD:D_SOD-323","1",""
"D10","D_Small","Diode_SMD:D_SOD-323","1",""
"D11","D_Small","Diode_SMD:D_SOD-323","1",""
"D12","D_Small","Diode_SMD:D_SOD-323","1",""
"D13","D_Small","Diode_SMD:D_SOD-323","1",""
"D14","D_Small","Diode_SMD:D_SOD-323","1",""
"D15","D_Small","Diode_SMD:D_SOD-323","1",""
"D16","D_Small","Diode_SMD:D_SOD-323","1",""
"D17","D_Small","Diode_SMD:D_SOD-323","1",""
"D18","D_Small","Diode_SMD:D_SOD-323","1",""
"D19","D_Small","Diode_SMD:D_SOD-323","1",""
"D20","D_Small","Diode_SMD:D_SOD-323","1",""
"D21","D_Small","Diode_SMD:D_SOD-323","1",""
"D22","D_Small","Diode_SMD:D_SOD-323","1",""
"D23","D_Small","Diode_SMD:D_SOD-323","1",""
"D24","D_Small","Diode_SMD:D_SOD-323","1",""
"D25","D_Small","Diode_SMD:D_SOD-323","1",""
"D26","D_Small","Diode_SMD:D_SOD-323","1",""
"D27","D_Small","Diode_SMD:D_SOD-323","1",""
"D28","D_Small","Diode_SMD:D_SOD-323","1",""
"D29","D_Small","Diode_SMD:D_SOD-323","1",""
"D30","D_Small","Diode_SMD:D_SOD-323","1",""
"D31","D_Small","Diode_SMD:D_SOD-323","1",""
"D32","D_Small","Diode_SMD:D_SOD-323","1",""
"D33","D_Small","Diode_SMD:D_SOD-323","1",""
"D34","D_Small","Diode_SMD:D_SOD-323","1",""
"D35","D_Small","Diode_SMD:D_SOD-323","1",""
"D36","D_Small","Diode_SMD:D_SOD-323","1",""
"D37","D_Small","Diode_SMD:D_SOD-323","1",""
"D38","D_Small","Diode_SMD:D_SOD-323","1",""
"D39","D_Small","Diode_SMD:D_SOD-323","1",""
"D40","D_Small","Diode_SMD:D_SOD-323","1",""
"F1","500mA","Fuse:Fuse_1206_3216Metric","1",""
"H1","MountingHole","MountingHole:MountingHole_2.2mm_M2_ISO7380","1",""
"H2","MountingHole","MountingHole:MountingHole_2.2mm_M2_ISO7380","1",""
"H3","MountingHole","MountingHole:MountingHole_2.2mm_M2_ISO7380","1",""
"H4","MountingHole","MountingHole:MountingHole_2.2mm_M2_ISO7380","1",""
"H5","MountingHole","MountingHole:MountingHole_2.2mm_M2_ISO7380","1",""
"H6","MountingHole","MountingHole:MountingHole_2.2mm_M2_ISO7380","1",""
"J2","Waveshare 2in LCD (ST7789V)","Connector_PinHeader_2.54mm:PinHeader_1x08_P2.54mm_Vertical","1",""
"R1","10k","Resistor_SMD:R_0402_1005Metric","1",""
"R4","22R","Resistor_SMD:R_0402_1005Metric","1",""
"R5","22R","Resistor_SMD:R_0402_1005Metric","1",""
"R6","10k","Resistor_SMD:R_0402_1005Metric","1",""
"SW1","SW_Push","keyswitches:Kailh_socket_PG1350","1",""
"SW2","SW_Push","keyswitches:Kailh_socket_PG1350","1",""
"SW3","SW_Push","keyswitches:Kailh_socket_PG1350","1",""
"SW4","SW_Push","keyswitches:Kailh_socket_PG1350","1",""
"SW5","SW_Push","keyswitches:Kailh_socket_PG1350","1",""
"SW6","SW_Push","keyswitches:Kailh_socket_PG1350","1",""
"SW7","SW_Push","keyswitches:Kailh_socket_PG1350","1",""
"SW8","SW_Push","keyswitches:Kailh_socket_PG1350","1",""
"SW9","SW_Push","keyswitches:Kailh_socket_PG1350","1",""
"SW10","SW_Push","keyswitches:Kailh_socket_PG1350","1",""
"SW11","SW_Push","keyswitches:Kailh_socket_PG1350","1",""
"SW12","SW_Push","keyswitches:Kailh_socket_PG1350","1",""
"SW13","SW_Push","keyswitches:Kailh_socket_PG1350","1",""
"SW14","SW_Push","keyswitches:Kailh_socket_PG1350","1",""
"SW15","SW_Push","keyswitches:Kailh_socket_PG1350","1",""
"SW16","SW_Push","keyswitches:Kailh_socket_PG1350","1",""
"SW17","SW_Push","keyswitches:Kailh_socket_PG1350","1",""
"SW18","SW_Push","keyswitches:Kailh_socket_PG1350","1",""
"SW19","SW_Push","keyswitches:Kailh_socket_PG1350","1",""
"SW20","SW_Push","keyswitches:Kailh_socket_PG1350","1",""
"SW21","SW_Push","keyswitches:Kailh_socket_PG1350","1",""
"SW22","SW_Push","keyswitches:Kailh_socket_PG1350","1",""
"SW23","SW_Push","keyswitches:Kailh_socket_PG1350","1",""
"SW24","SW_Push","keyswitches:Kailh_socket_PG1350","1",""
"SW25","SW_Push","keyswitches:Kailh_socket_PG1350","1",""
"SW26","SW_Push","keyswitches:Kailh_socket_PG1350","1",""
"SW27","SW_Push","keyswitches:Kailh_socket_PG1350","1",""
"SW28","SW_Push","keyswitches:Kailh_socket_PG1350","1",""
"SW29","SW_Push","keyswitches:Kailh_socket_PG1350","1",""
"SW30","SW_Push","keyswitches:Kailh_socket_PG1350","1",""
"SW31","SW_Push","keyswitches:Kailh_socket_PG1350","1",""
"SW32","SW_Push","keyswitches:Kailh_socket_PG1350","1",""
"SW33","SW_Push","keyswitches:Kailh_socket_PG1350","1",""
"SW34","SW_Push","keyswitches:Kailh_socket_PG1350","1",""
"SW35","SW_Push","keyswitches:Kailh_socket_PG1350","1",""
"SW36","SW_Push","keyswitches:Kailh_socket_PG1350","1",""
"SW37","SW_Push","keyswitches:Kailh_socket_PG1350","1",""
"SW38","SW_Push","keyswitches:Kailh_socket_PG1350","1",""
"SW39","SW_Push","keyswitches:Kailh_socket_PG1350","1",""
"SW40","SW_Push","keyswitches:Kailh_socket_PG1350","1",""
"U1","ATmega32U4-M","Package_DFN_QFN:QFN-44-1EP_7x7mm_P0.5mm_EP5.2x5.2mm","1",""
"U2","PocketBeagle 2","Module:BeagleBoard_PocketBeagle","1",""
"Y1","16MHz","Crystal:Crystal_SMD_3225-4Pin_3.2x2.5mm","1",""

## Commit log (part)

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2022-10-11 init commit
2022-10-19 add gerbers
2022-12-05 add case files
2023-10-22 add minipeg48 and kowgary16
2023-10-22 add minipeg48 + kowgary16 image
2023-12-05 add vial firmware files
2023-12-06 improve firmware docs
